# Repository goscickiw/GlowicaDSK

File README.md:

# GlowicaDSK
Głowica DSK do antenowych instalacji zbiorowych

Repozytorium ma na celu umożliwienie dostępu do informacji na temat tego dawno zapomnianego urządzenia.

Głowica DSK była wykorzystywana w antenowych instalacjach zbiorowych (AIZ) w celu podłączenia do instalacji anteny prętowej na fale długie, średnie i krótkie (często mylonej z piorunochronem) oraz anteny dipolowej UKF. Głowica taka składa się z iskiernika zabezpieczającego przed przepięciami, dwóch transformatorów dopasowujących impedancję anteny DSK na różnych zakresach częstotliwości oraz trzech filtrów - opisanych na schemacie.

Więcej informacji w plikach projektu.

Oryginał:

Sposób montażu:

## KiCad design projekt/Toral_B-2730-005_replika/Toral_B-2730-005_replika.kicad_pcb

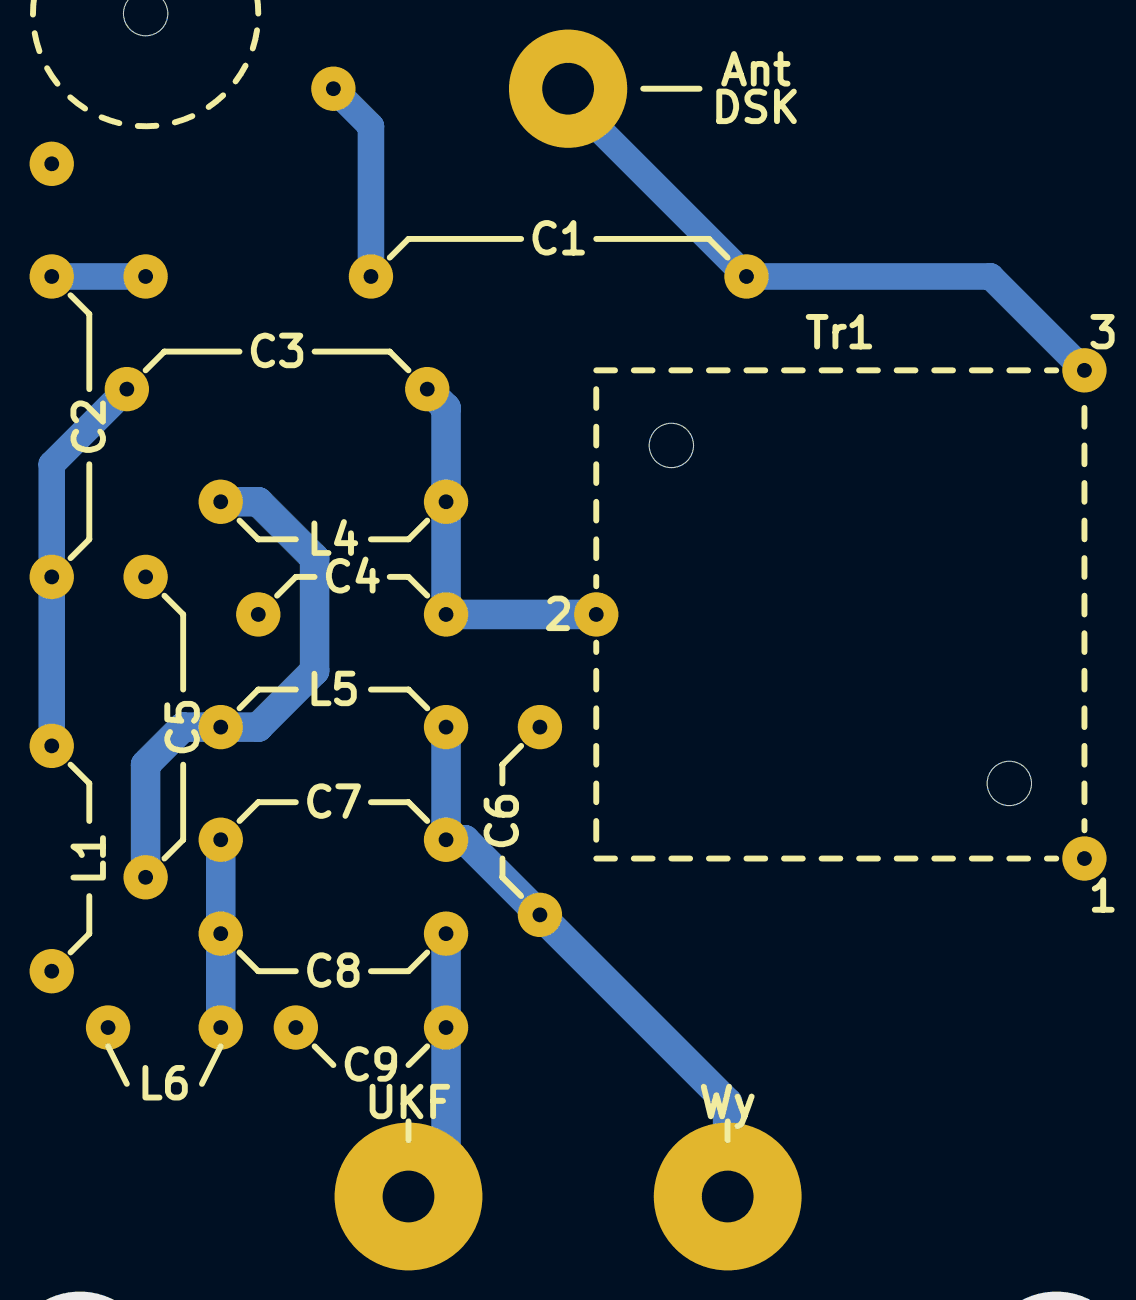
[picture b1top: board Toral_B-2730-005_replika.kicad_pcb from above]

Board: 2 copper layers, 18 parts (0 on the bottom side), 10 nets.

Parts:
AE1: Antena prętowa DSK; Antena
C1: 68pF; 2pin_25mm
C2, C3: 560pF; 2pin_20mm
C4, C6: 27pF; 2pin_13mm
C5: 100pF; 2pin_20mm
C7, C8: 51pF; 2pin_15mm
C9: 15pF; 2pin_10mm
J1: UKF; Pad
J2: Wy; Pad
L1: L_Core_Ferrite; 2pin_15mm
L4, L5: L; 2pin_15mm
L6: L; 2pin_7.5mm
Tr1: Tr1
Tr2: Tr2

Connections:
GND: C4.1, C5.1, C6.2, C9.2, L1.2, L6.2, Tr1.1, Tr2.1
unnamed: AE1.1, C1.2, Tr1.3
unnamed: C1.1, Tr2.3
unnamed: C2.1, Tr2.2
unnamed: C2.2, C3.1, L1.1
unnamed: C3.2, C4.2, L4.1, Tr1.2
unnamed: C5.2, L4.2, L5.1
unnamed: C6.1, C7.2, J2.1, L5.2
unnamed: C7.1, C8.2, L6.1
unnamed: C8.1, C9.1, J1.1

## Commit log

2020-08-22 Projekt, zdjęcia oryginalnej głowicy, skan z książki
2020-08-23 Poprawki w oznaczeniach elementów
2020-08-23 Schemat PDF
2020-08-23 Aktualizacja opisu
